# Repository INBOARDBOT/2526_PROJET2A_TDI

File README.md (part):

# 2526_PROJET2A_TDI
Total Drive Immersion - Motion System

The objective of this project is to create a 3 axis motion plateform for car racing simulations.
It consist of four linear actuators (with their respective [**drivers**](https://github.com/INBOARDBOT/2526_PROJET2A_TDI/tree/main/HARDWARE/PCB'S/FOC_CONTROLLER_V2)), a Nucleo Discovery which handle
the communication between the drivers and the computer as well as a touchscreen interface.
The data is sent from SimHub to the the Nucleo via UART. The position values are then distributed to each actuator via an [**RS485**](https://github.com/INBOARDBOT/2526_PROJET2A_TDI/tree/main/HARDWARE/PCB'S/COM_BOARD) bus.

# Achitecture logicielle

L'architecture logicielle est conçue de manière modulaire, segmentant les fonctionnalités du simulateur de conduite en plusieurs sous-systèmes spécialisés. Cette approche permet de séparer les responsabilités et de faciliter la maintenance du système. L'architecture s'articule autour de trois piliers principaux :

Couche Communication : Gère les protocoles d'échange de données entre l'unité centrale et les drivers de vérins (via le bus RS-485), garantissant l'intégrité et la rapidité des transmissions.

Module de Gestion des Actionneurs : Assure le traitement des commandes, le calcul des trajectoires des vérins et le monitoring de l'état des drivers.

Interface Graphique et IHM : Pilote le rendu visuel sur l'écran LCD-TFT et traite les interactions tactiles de l'utilisateur, tout en gérant les ressources stockées en mémoire Flash.

## Organistaion du projet
<br>
* `Application/` Contient la logique métier principale développée par l'utilisateur.
    * `gui/` et `generated/` Dédiés à l'interface graphique (typiquement pilotés par TouchGFX sur le F746G). Regroupe le backend (logique) et le frontend (assets et code généré).
    * `Core/` Noyau de l'application gérant la communication et la supervision de la centrale avec le reste du système de simulation.
* `Driver/` Regroupe les couches d'abstraction matérielle (BSP : gestion des composants externes). 
* `Debug/` Répertoire de sortie du compilateur.

## Présentation des Composants

### Unité Centrale
<br>
La centrale controle l'enssemble du systeme de simulation, elle doit etre reactive et embarquer une interface graphique servant d'IHM. Voici donc les principales fonctionnalites que la carte STM32F746G nous propose :
* Puissance de calcul : Architecture Arm Cortex STM32F746NGH6
* Interactions avec l'utilisateur (IHM) : Ecran tactile 4.3” RGB 480×272 color LCD-TFT
* Stockage des ressources graphiques lourdes commes les imges : 128-Mbit Quad-SPI Flash memory

Fonctionnalitees addiotionnelles petinentes :
* Gestion Audio intégrée : Audio line in and line out jack & Stereo speaker outputs

### Driver de vérin
<br>
Les drivers des verrins permettent de faire l'interface entre les ordres transmis par la centrale et l'action entrepris par les verrins. 
Les drivers des verrins permettent de communiquer via le bus RS485 afin de recevoir les données de position et de renvoyer des informations sur l'etat de l'actionneur.Il est compose des elements suivants :
* STSPIN32G4: Gère les calculs d'asservissemntet  le controle de l'etage de puissance grâce a son driver de mosfet intégré.
* STL130N8F7: L'etage de puissance est composé de trois demi pont avec des N-MOS pouvant supporter jusqu'a 80V et 100A 
* THVD1420: Tranciever RS485 

### Interface de Communication (Bus RS-485)
<br>
L'interface de communication est une carte électronique intermédiaire positionnée entre l'unité centrale et les différents actionneurs (vérins).

Pour surmonter la contrainte de la distance physique et garantir une transmission rapide et immunisée contre les parasites, la liaison s'appuie sur la norme RS-485. Ce standard utilise une signalisation différentielle particulièrement fiable en milieu industriel.

L'interface assure la conversion des signaux : elle transforme le protocole UART (TTL) de la centrale en signaux différentiels pour le bus, puis les drivers des vérins effectuent la conversion inverse pour traiter l'information. L'ensemble des drivers est raccordé en parallèle selon une topologie en bus, permettant une gestion simplifiée du câblage.

## Environnement de Développement
Le développement du projet repose sur une chaîne d'outils intégrée, permettant de gérer aussi bien la configuration matérielle que l'interface utilisateur et le versionnage du code.

`STM32CubeIDE` <br>
Il s'agit de l'environnement de développement (IDE) fourni par STMicroelectronics.

* Configuration : Intègre STM32CubeMX pour configurer graphiquement les périphériques (UART, RS-485, Horloges).

* Développement & Debug : Permet l'écriture du code en C/C++ et offre des outils de débogage avancés (lecture de registres en temps réel, analyseur de variables).

`TouchGFX Designer` <br>
Framework graphique avancé spécifiquement optimisé pour les microcontrôleurs STM32.

* Design UI : Permet de concevoir l'interface de manière visuelle pour ensuite developper en C++ dessus.

* CMSIS-RTOS : S'intègre avec FreeRTOS pour séparer le thread de rendu graphique des threads de communication et de calcul (Backend/Frontend).

* Generation du fichier du projet : Génére le code d'initialisation avec la configuration de l'interface graphique automatise (gros avantage de TouchGFX).

# Interface Graphique
<br>
L'interface graphique (IHM) permet de visualiser en temps réel l'état du système de simulation. Elle offre à l'utilisateur une plateforme interactive pour piloter le simulateur, lancer les procédures de calibration et ajuster les paramètres de conduite.

## TouchGFX Designer
TouchGFX Designer est l'outil utilisé pour concevoir l'environnement visuel. Il génère un code C++ optimisé qui tire parti des capacités d'accélération matérielle du STM32.

### Creation du projet
La première étape consiste à sélectionner le BSP (Board Support Package) correspondant à notre matériel : le `STM32F746G Discovery Kit`.<br>
<br>

[!IMPORTANT] Cette étape est cruciale car TouchGFX génère non seulement l'interface, mais aussi toute la structure du projet (fichiers de configuration, drivers d'écran, gestion de la mémoire) que nous importerons ensuite dans STM32CubeIDE.

### Architecture de l'interface
L'interface est découpée en plusieurs Écrans (Screens). Chaque écran possède son propre fichier de vue (View) et son présentateur (Presenter), permettant de séparer la logique graphique de la logique métier.

#### Ecran
Les vues du simulateur
Pour garantir une navigation fluide, nous avons segmenté l'IHM en quatre écrans principaux :

* SimHubScreen : Le tableau de bord principal. Il affiche les données télémétriques en temps réel, telles que l'extension des vérins et la consommation électrique des drivers.

* LoadingScreen : Une interface de transition utilisée lors des processus lourds, typiquement durant la phase de calibration automatique des vérins.

* MenuScreen : Le point d'entrée central permettant à l'utilisateur de naviguer entre les différentes sections.

* SettingScreen : Un espace dédié à la configuration logicielle et matérielle du système.

<br>

Avoir une multitude d'ecran permet de faciliter le developpement des differents UI. 

#### Composants et Outils
L'IDE propose deux types de blocs de construction pour concevoir les écrans :

1. Les Widgets : Ce sont les éléments de base (boutons, zones de texte, jauges, formes géométriques). Ils sont entièrement personnalisables pour correspondre à la charte graphique du simulateur.

2. Les Conteneurs (Containers) : Ils permettent de regrouper plusieurs widgets au sein d'une même entité. Cela facilite la création de fenêtres modales, de listes déroulantes ou de menus complexes.

Vous pouvez retrouver ci-dessous la documentation sur les outils et conteneurs pour en apprendre d'avantages [Contenuer/Outil](https://support.touchgfx.com/docs/development/ui-development/working-with-touchgfx/widgets-and-containers)

### Generer le projet
Une fois le design finalisé, l'outil génère le code source. Ce processus inclut :

* La conversion des images en tableaux de données stockés en Flash QSPI.

* L'implémentation de l'API graphique compatible avec FreeRTOS.

* La configuration des périphériques de la carte (écran, tactile, DMA2D).

[!NOTE] Bien que TouchGFX Designer soit puissant, il se limite à la couche visuelle. Les interactions complexes (ex: cliquer sur un bouton pour activer un vérin) nécessitent une implémentation manuelle dans le code C++ généré, via des fonctions de rappel (Callbacks).

## Backend and Frontend communication
Le défi majeur consiste à faire communiquer l'interface utilisateur avec le reste du système (capteurs, bus RS-485). TouchGFX utilise une architecture structurée pour séparer l'affichage de la logique métier.<br>

Définitions
* Le Frontend (La Vue) : Comprend les composants visibles à l'écran. Il est responsable de l'affichage des données et de la capture des interactions utilisateur.

* Le Backend (Le Système) : Représente tout ce qui se passe en dehors de l'interface (réception des données RS-485, calculs de trajectoires, mesures de courant).

L'Architecture MVP (Model-View-Presenter)<br>
<br>
Pour assurer une synchronisation fluide sans bloquer l'affichage, TouchGFX s'appuie sur trois couches :

1. Le Model : C'est le point d'entrée du Backend. Il reçoit les événements extérieurs (ex: nouvelle mesure de courant) et les stocke temporairement.

2. Le Presenter : Il agit comme un pont. Il surveille les changements dans le Model et ordonne à la View de se mettre à jour.

3. La View : Elle reçoit les ordres du Presenter et modifie visuellement les widgets (ex: mettre à jour la valeur d'une jauge).

vous pouvez visualiser cette video qui explique en detail comment afficher une valeur sur l'interface graphique [video](https://www.youtube.com/watch?v=Y7d6-59YQu8)

# Protocole de Communication
Comme expliqué précédemment, la liaison entre la centrale et les drivers repose sur une couche physique RS-485. Bien que les signaux en entrée et en sortie de l'interface soient au format UART, le support physique RS-485 permet de transporter ces données sur de longues distances tout en supportant une topologie réseau de type "Bus".

## Architecture Maître-Esclave
Pour organiser les échanges sur ce canal partagé, nous utilisons une architecture Maître-Esclave :

* Le Maître (Centrale) : Il est l'unique initiateur de la communication. Il interroge ou envoie des ordres aux drivers.

* Les Esclaves (Drivers) : Ils "écoutent" en permanence le bus et ne répondent ou n'agissent que lorsqu'ils sont explicitement sollicités par le maître.

## Principe du Bus de Communication 
Dans cette configuration, tous les esclaves sont branchés en parallèle sur la même ligne physique. Pour éviter que tous les vérins ne s'activent en même temps, nous utilisons un système d'adressage et de trames de données : <br>
<br>

1. L'Adressage : Chaque driver possède un identifiant unique (ID). Le message envoyé par la centrale commence par l'adresse de destination.

2. Le Filtrage : Tous les drivers reçoivent le signal, mais seul l'esclave dont l'adresse correspond à celle contenue dans le message traite l'information. Les autres ignorent la trame.

3. Les Données (Payload) : Une fois l'adresse validée, l'esclave décode les instructions (ex: consigne de position, vitesse, ou demande d'état).

## Gestion du flux (Half-Duplex)
<br>
Le bus RS-485 utilisé est généralement Half-Duplex : la centrale et les drivers partagent la même paire de fils pour émettre et recevoir.

Point d'attention : La centrale doit libérer le bus (repasser en mode réception) immédiatement après avoir envoyé une commande pour permettre à l'esclave de renvoyer son accusé de réception ou ses données de télémétrie.

## Structure de communication
<p align="justify">Afin d'optimiser les échanges de données avec les quatre esclaves du système, nous utilisons un protocole de cycle séquentiel. Le maître initie une transmission/réception itérative de l'esclave 0 à l'esclave 3. Au cours de chaque cycle, le maître récupère l'intégralité des données de l'esclave ciblé et les traite avant de passer au suivant. </p>

### Paquet de Données
<p align="justify">Le paquet de données est l'élément central de notre protocole. Il agit comme un conteneur standardisé permettant de transporter efficacement les commandes et les retours d'état.</p>

Voici la structure logicielle du paquet :

```
typedef struct __attribute__((packed))
{
    uint8_t startByte;   
    uint8_t address;     
    uint8_t cycleId;     
    
    uint8_t statusFlags; 
    uint8_t payloadCount; 

    union {
        struct {
            uint8_t type;    
            uint8_t code;    
        } fifoEntries[MAX_DATA / 2];

        uint16_t infoArray[MAX_DATA / 2]; 
        
        uint8_t rawBytes[MAX_DATA];
    } payload;

    uint8_t checksum;
    uint8_t stopByte;    
} MotionPacket_t;
```

Caractéristiques de Transmission
* <p align="justify">Standard UART : Le type uint8_t est utilisé comme unité de base, conformément au standard de communication série UART.</p>

* <p align="justify">Résolution des données : Les données système (telles que celles fournies par SimHub) sont quantifiées sur 16 bits. Par conséquent, chaque valeur dans infoArray occupe deux octets (uint8_t) lors de la transmission série.</p>

### Flag 
Les `Flags` ou `Drapeaux` en francais sont des informations actuelles sur le systeme d'une longueur d'un seul bit. Voici les differents que s'echangent le master et les slaves.

_Flag Master_
| Flag info     | Position bit  |
| ------------- |:-------------:|
| ACK_REQUEST   | 0             |
| CYCLE_ID_RST  | 1             |
| EMPTY_DATA    | 2             |
| TO_DEFINE     | 3             |
| TO_DEFINE     | 4             |
| TO_DEFINE     | 5             |
| TO_DEFINE     | 6             |
| TO_DEFINE     | 7             |

EMPTY_DATA   : Inform the slave it doesn't need to look for data in the packet <br>
CYCLE_ID_RST : Inform the slave the cycle id is reset (to 0) <br>
ACK_REQUEST  : Inform the slave to respond with flag ACK <br>

_Flag Slave_
| Flag info     | Position bit  |
| ------------- |:-------------:|
| ACK           | 0             |
| INIT_DONE     | 1             |
| MOTOR_EN      | 2             |
| MOTOR_MOVING  | 3             |
| BUSY          | 4             |
| EMPTY_DATA    | 5             |
| EMPTY_STATUS  | 6             |
| TO_DEFINE     | 7             |

ACK          : Inform the master that his message is acknowledged<br>
INIT_DONE    : Inform the master the initialisation is done (the system is calibrated)<br>
MOTOR_EN     : Inform the master that the motor are enabled to move<br>
MOTOR_MOVING : Inform the master the motor are moving<br>
BUSY         : Inform the master the slave can't take instruction at the moment<br>
EMPTY_DATA   : Inform the master to not look for data<br>
EMPTY_STATUS : Inform the master to not look for errors or events<br>

### Evenements
Les événements sont des alertes asynchrones envoyées par les esclaves pour informer d'un changement d'état opérationnel.<br>

Voici la liste evenements :
_Flag Slave_
| Evenement              | Code           |
| ---------------------- |:--------------:|
| EVT_NONE               | 0x00           |
| EVT_MOVEMENT_STARTED   | 0x01           |
| EVT_MOVEMENT_COMPLETED | 0x02           |
| EVT_TARGET_REACHED     | 0x03           |
| EVT_LIMIT_SWITCH_MIN   | 0x04           |
| EVT_LIMIT_SWITCH_MAX   | 0x05           |
| EVT_HOMING_STARTED     | 0x06           |
| EVT_HOMING_COMPLETED   | 0x07           |
| EVT_DRIVER_ONLINE      | 0x08           |
| EVT_DRIVER_OFFLINE     | 0x09           |
| EVT_PARAM_CHANGED      | 0x0A           |
| EVT_PLAYMODE_ON        | 0x0B           |
| EVT_PLAYMODE_OFF       | 0x0C           |
| EVT_INITMODE_ON        | 0x0D           |
| EVT_INITMODE_OFF       | 0x0E           |
| EVT_SLEEPMODE_ON       | 0x0F           |
| EVT_SLEEPMODE_OFF      | 0x10           |
| EVT_CALIB_STARTED      | 0x11           |
| EVT_CALIB_COMPLETED    | 0x12           |
| EVT_PARKED             | 0x13           |

EVT_NONE : No event <br>              
EVT_MOVEMENT_STARTED : The slave piston has started its movement <br>  
EVT_MOVEMENT_COMPLETED : The slave piston has completed its movement<br>
EVT_TARGET_REACHED : The slave piston is a the requested position<br>    
EVT_LIMIT_SWITCH_MIN : The slave piston is at the minimum position<br>  
EVT_LIMIT_SWITCH_MAX : The slave piston is at the maximum position<br>  
EVT_HOMING_STARTED : The slave piston is performing homing<br>    
EVT_HOMING_COMPLETED : The slave piston has completed its homing<br>  
EVT_DRIVER_ONLINE : The slave is now offline wait to be restarted<br>     
EVT_DRIVER_OFFLINE : The slave is now online and can perform operation <br>     
EVT_PARAM_CHANGED : The slave has succesfully changed its parameter <br>     
EVT_PLAYMODE_ON : The slave is ready for gaming <br>     
EVT_PLAYMODE_OFF : The slave is not ready for gaming <br>     

### Erreurs
Les erreurs sont des alertes asynchrones signalant un dysfonctionnement ou une anomalie sur un esclave.<br>

Voici la liste erreurs :
| Erreur                 | Code           |
| ---------------------- |:--------------:|
| ERR_NONE               | 0x00           |
| ERR_INVALID_COMMAND    | 0x01           |
| ERR_INVALID_PARAM      | 0x02           |
| ERR_TIMEOUT            | 0x03           |
| ERR_CHECKSUM_FAIL      | 0x04           |
| ERR_UNSUPPORTED        | 0x05           |
| ERR_STALL_DETECTED     | 0x06           |
| ERR_UNDERVOLTAGE       | 0x07           |
| ERR_UNDERVOLTAGEMCU    | 0x08           |
| ERR_FAILED_CALIB       | 0x09           |
| ERR_FAILED_SET_PIS_POS | 0x0A           |
| ERR_COMM_LOST          | 0x0B           |
| ERR_FRAME_INVALID      | 0x0C           |
| ERR_OVERHEATING        | 0x10           |
| ERR_OVERCURRENT        | 0x11           |
| ERR_OVERVOLTAGE        | 0x12           |
| ERR_OVERVOLTAGEMCU     | 0x13           |

Les erreurs critiques se différencient par le préfixe 0x1-. Elles entraînent généralement une mise en sécurité immédiate du matériel.<br>

ERR_NONE : No error <br>
ERR_INVALID_COMMAND : Command instruction not found <br>    
ERR_INVALID_PARAM : Packet parameter is invalid <br>      
ERR_TIMEOUT : Slave sends it when it takes too much time to do an operation<br>            
ERR_CHECKSUM_FAIL : Checksum of packet failed <br>              
ERR_STALL_DETECTED : Piston does not move even though it is instructed to (physical struggle) <br>    
ERR_UNDERVOLTAGE : Piston under voltage <br>      
ERR_UNDERVOLTAGEMCU : MCU is under voltage <br>   
ERR_FAILED_CALIB : Slave failed calibration <br>      
ERR_FAILED_SET_PIS_POS : Slave failed to set to the correct position <br>
ERR_COMM_LOST : Slave lost communication with master <br>         
ERR_FRAME_INVALID : Packet structure is giberish <br>     
ERR_OVERHEATING : Critic error piston is over heating <br>       
ERR_OVERCURRENT : Critic error piston is short circuiting <br>       
ERR_OVERVOLTAGE : Critic error piston is over voltage <br>       
ERR_OVERVOLTAGEMCU : Critic error MCU is over voltage <br>    

### Commandes

Les commandes sont les mots cles dans les paquets de transmission d'informations entre la centrale et les drivers.<br>

Voici la liste des differentes commandes :
| Commandes | Code | User |
| :--- | :---: | :--- |
| CMD_NOP | `0x00` | Master |
| CMD_PING | `0x01` | Master |
| CMD_GET_INFO | `0x02` | Master |
| CMD_RETURN_INFO | `0x03` | Slave |
| CMD_SET_STATE | `0x04` | Master |
| CMD_SET_MOTOR | `0x05` | Master |
| CMD_SET_PISTON | `0x06` | Master |

CMD_NOP : No cmd <br>
CMD_PING : Ping driver, waits for ping back to verify communication. Possibility to add a custom message to pinged device. data(64B, optional) : char* <br>
CMD_GET_INFO : Master request data from driver. data(1B) :  <br> 
| Instruction            | Position bit   |
| ---------------------- |:--------------:|
| POSITION               | 0              |
| SPEED                  | 1              |
| ACCELERATION           | 2              |
| TEMPERATURE            | 3              |
| MCU_VOLTAGE            | 4              |
| DRIVER_VOLTAGE         | 5              |
| DRIVER_STATE           | 6              |
| UNDEFINED              | 7              |
<br>

CMD_RETURN_INFO : Driver respond with requested data. data(14B) : <br>
| Instruction            | Position byte  |
| ---------------------- |:--------------:|
| POSITION               | 0-1            |
| SPEED                  | 2-3            |
| ACCELERATION           | 4-5            |
| TEMPERATURE            | 6-7            |
| MCU_VOLTAGE            | 8-9            |
| DRIVER_VOLTAGE         | 10-11          |
| DRIVER_STATE           | 12-13          |
| UNDEFINED              | ---            |
<br>
Pay attention that the response uses a `variable-length packed format`. But the requested values are appended sequentially without gaps. For example, requesting only POSITION and DRIVER_STATE will result in a 4-byte payload where the state immediately follows the position.

CMD_SET_STATE : Set the state of the driver. IN (1B) :  <br> 
| Instruction            | Position bit   |
| ---------------------- |:--------------:|
| SLEEP                  | 0              |
| INIT                   | 1              |
| PLAY                   | 2              |
| UNDEFINED              | 3              |
| UNDEFINED              | 4              |
| UNDEFINED              | 5              |
| UNDEFINED              | 6              |
| UNDEFINED              | 7              |
<br>

CMD_SET_MOTOR : Set the configuration of the motor. IN (1B) :  <br> 
| Instruction            | Position bit   |
| ---------------------- |:--------------:|
| MOTOR_ENABLE           | 0              |
| MOTOR_MOVEMENT         | 1              |
| UNDEFINED              | 2              |
| UNDEFINED              | 3              |
| UNDEFINED              | 4              |
| UNDEFINED              | 5              |
| UNDEFINED              | 6              |
| UNDEFINED              | 7              |
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
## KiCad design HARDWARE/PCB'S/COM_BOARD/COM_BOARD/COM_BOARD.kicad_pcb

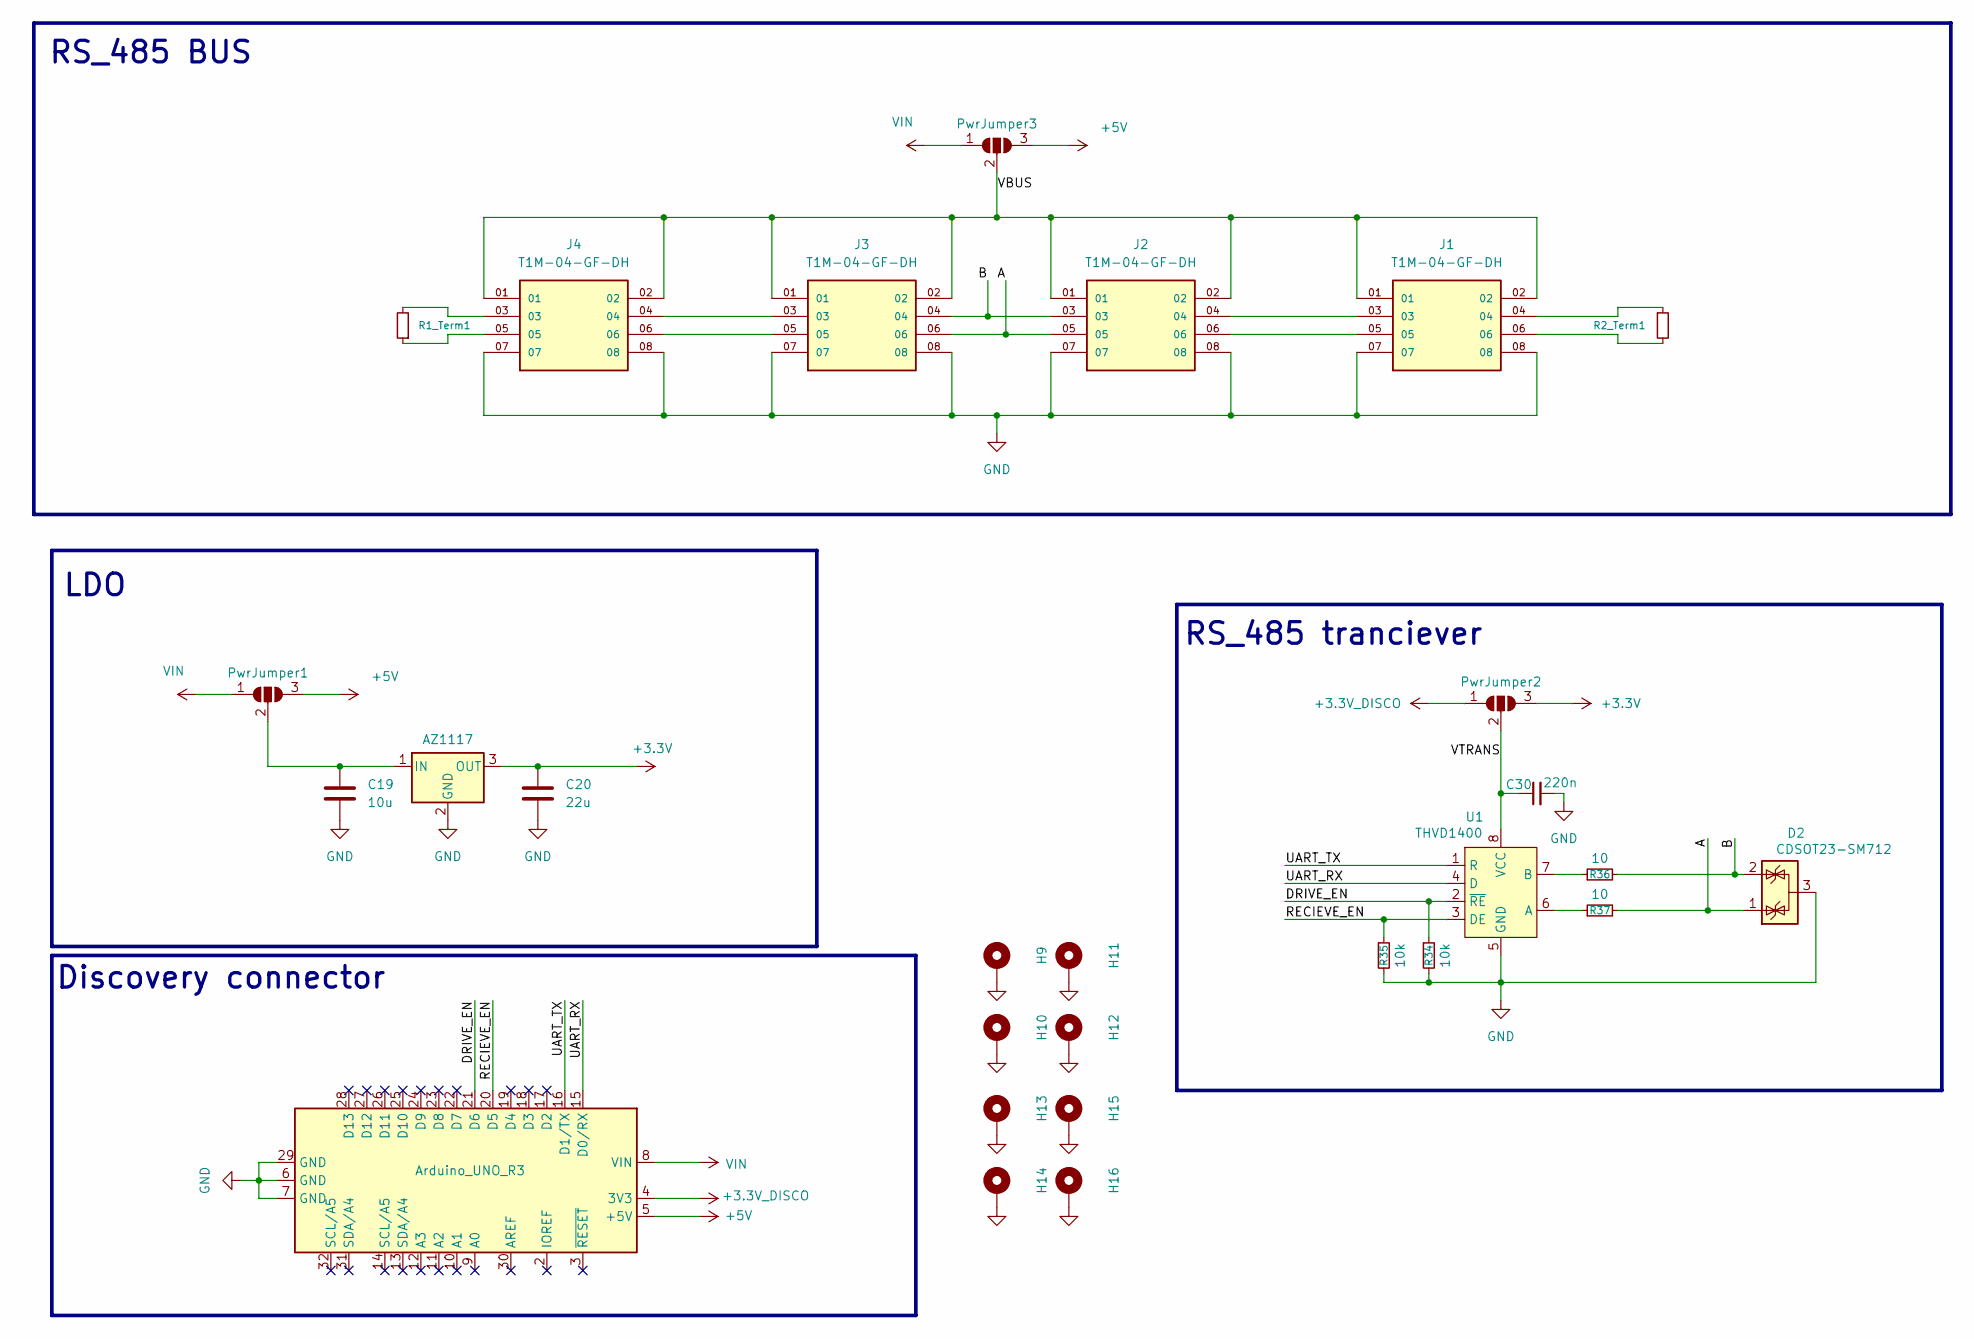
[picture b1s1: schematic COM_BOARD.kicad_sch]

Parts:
A1: Arduino_UNO_R3
C19: 10u; C_0805_2012Metric_Pad1.18x1.45mm_HandSolder
C20: 22u; C_0805_2012Metric_Pad1.18x1.45mm_HandSolder
C30: 220n; C_0603_1608Metric; MPN 885012207051
D2: CDSOT23-SM712; SOT-23
H9, H10, H11, H12, H13, H14, H15, H16: MountingHole_Pad; MountingHole_3.2mm_M3_Pad_Via
J1, J2, J3, J4: T1M-04-GF-DH; SAMTEC_T1M-04-GF-DH
J10: AZ1117; SOT-223
PwrJumper1, PwrJumper2, PwrJumper3: SolderJumper_3_Open; SolderJumper-3_P1.3mm_Open_RoundedPad1.0x1.5mm_NumberLabels
R1_Term1, R2_Term1: R_Small; R_0603_1608Metric
R34, R35: 10k; R_0603_1608Metric
R36, R37: 10; R_0603_1608Metric
U1: THVD1400; SOIC-8_3.9x4.9mm_P1.27mm

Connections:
+3.3V: C20.1, J10.3 (OUT), PwrJumper2.3 (B)
+3.3V_DISCO: A1.4 (3V3), PwrJumper2.1 (A)
+5V: A1.5 (+5V), PwrJumper1.3 (B), PwrJumper3.3 (B)
/A: D2.1 (K), J2.05, J3.06, R37.2
/B: D2.2 (K), J2.03, J3.04, R36.2
/DRIVE_EN: A1.21 (D6), R34.1, U1.2 (~RE)
/RECIEVE_EN: A1.20 (D5), R35.1, U1.3 (DE)
/UART_RX: A1.15 (D0/RX), U1.4 (D)
/UART_TX: A1.16 (D1/TX), U1.1 (R)
/VBUS: J1.01, J1.02, J2.01, J2.02, J3.01, J3.02, J4.01, J4.02, PwrJumper3.2 (C)
/VTRANS: C30.1, PwrJumper2.2 (C), U1.8 (VCC)
GND: A1.6 (GND), A1.7 (GND), A1.29 (GND), C19.2, C20.2, C30.2, D2.3 (A), H9.1, H10.1, H11.1, H12.1, H13.1, H14.1, H15.1, H16.1, J1.07, J1.08, J2.07, J2.08, J3.07, J3.08, J4.07, J4.08, J10.2 (GND), R34.2, R35.2, U1.5 (GND)
unnamed: J1.03, J2.04
unnamed: J1.04, R2_Term1.1
unnamed: J1.05, J2.06
unnamed: J1.06, R2_Term1.2
unnamed: J3.03, J4.04
unnamed: J3.05, J4.06
unnamed: J4.03, R1_Term1.2
unnamed: J4.05, R1_Term1.1
unnamed: C19.1, J10.1 (IN), PwrJumper1.2 (C)
unnamed: R37.1, U1.6 (A)
unnamed: R36.1, U1.7 (B)
VIN: A1.8 (VIN), PwrJumper1.1 (A), PwrJumper3.1 (A)

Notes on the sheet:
RS_485 tranciever
LDO
Discovery connector
RS_485 BUS

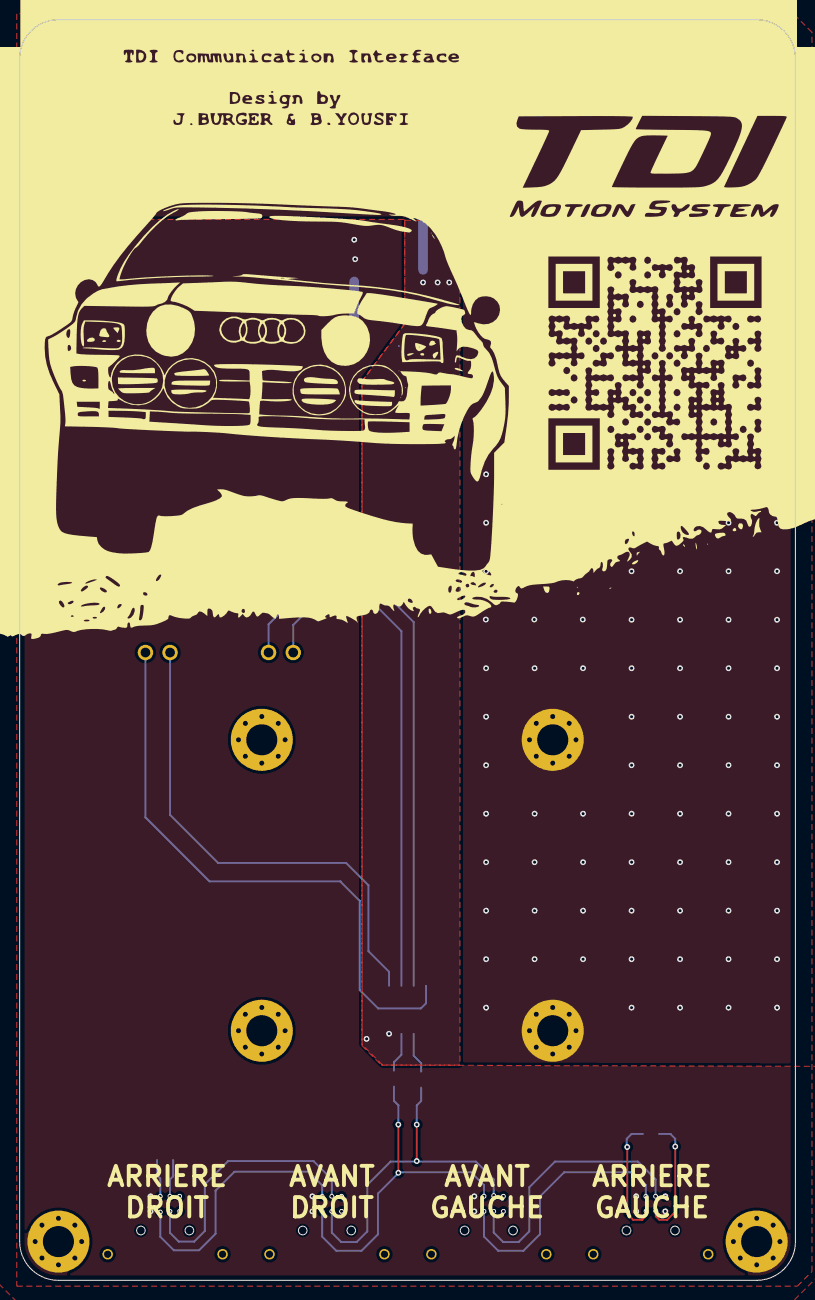
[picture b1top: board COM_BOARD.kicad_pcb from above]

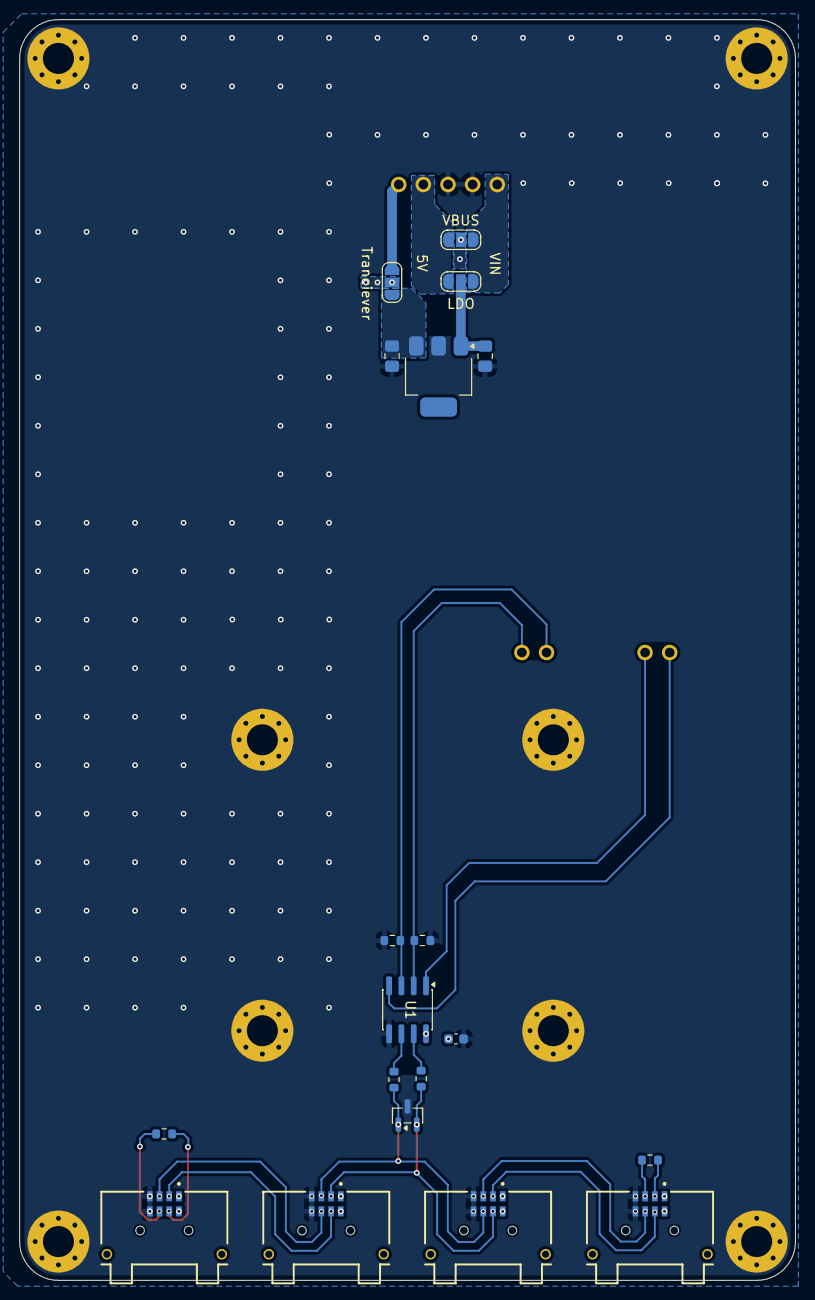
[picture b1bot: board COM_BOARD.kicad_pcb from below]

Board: 2 copper layers, 80.0 x 130.0 mm, 28 parts (20 on the bottom side), 24 nets.

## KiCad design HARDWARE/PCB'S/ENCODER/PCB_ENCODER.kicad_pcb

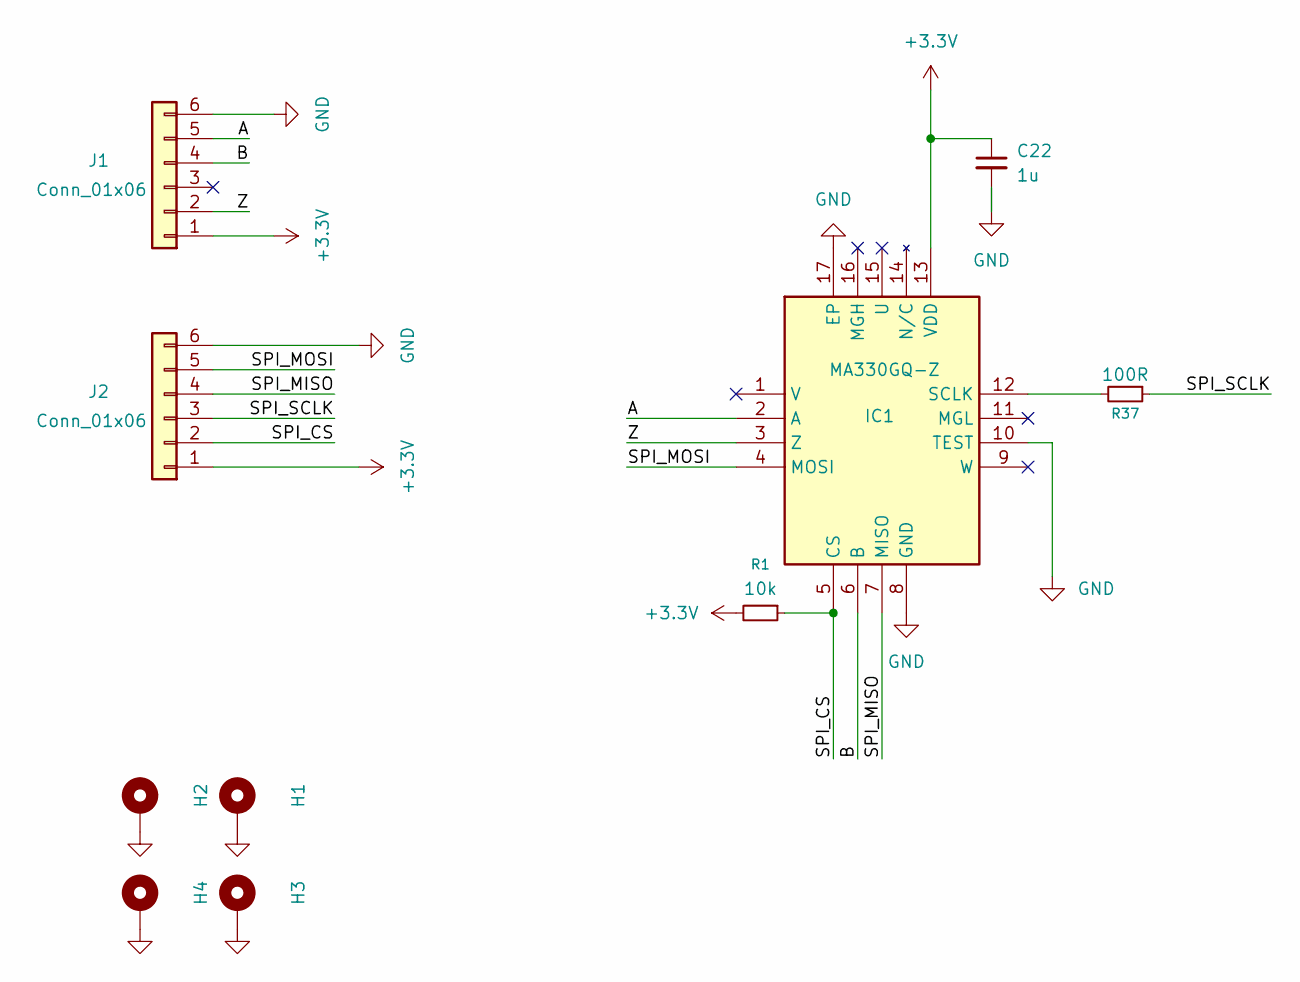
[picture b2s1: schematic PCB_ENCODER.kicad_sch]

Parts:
C22: 1u; C_0603_1608Metric
H1, H2, H3, H4: MountingHole_Pad; MountingHole_3.2mm_M3_Pad_Via
IC1: MA330GQ-Z; QFN-16-1EP_3x3mm_P0.5mm_EP1.7x1.7mm; Manufacturer_Part_Number MA330GQ-Z; Mouser Part Number 946-MA330GQ-Z
J1, J2: Conn_01x06; JST_GH_SM06B-GHS-TB_1x06-1MP_P1.25mm_Horizontal
R1: 10k; R_0603_1608Metric
R37: 100R; R_0603_1608Metric

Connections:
+3.3V: C22.1, IC1.13 (VDD), J1.1, J2.1, R1.2
/A: IC1.2 (A), J1.5
/B: IC1.6 (B), J1.4
/SPI_CS: IC1.5 (CS), J2.2, R1.1
/SPI_MISO: IC1.7 (MISO), J2.4
/SPI_MOSI: IC1.4 (MOSI), J2.5
/SPI_SCLK: J2.3, R37.1
/Z: IC1.3 (Z), J1.2
GND: C22.2, H1.1, H2.1, H3.1, H4.1, IC1.8 (GND), IC1.10 (TEST), IC1.17 (EP), J1.6, J2.6
unnamed: IC1.12 (SCLK), R37.2

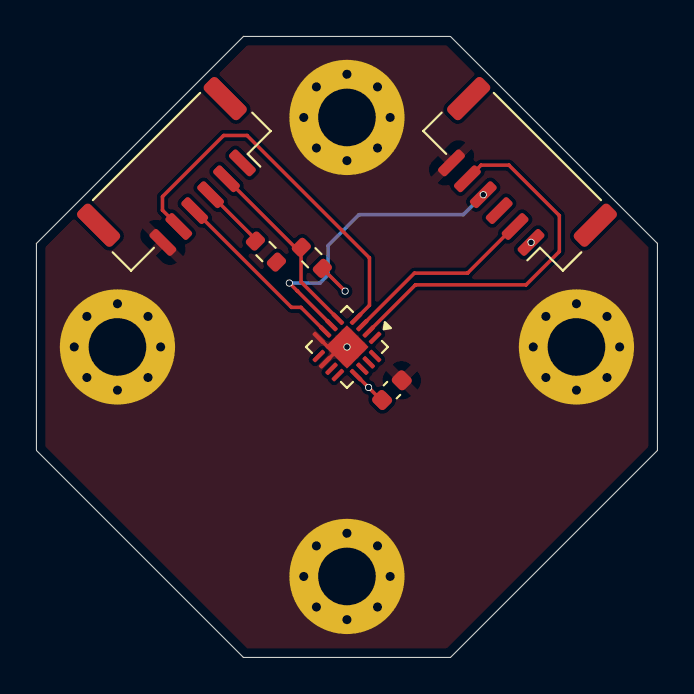
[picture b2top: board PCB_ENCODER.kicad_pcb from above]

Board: 2 copper layers, 34.5 x 34.5 mm, 10 parts (0 on the bottom side), 10 nets.

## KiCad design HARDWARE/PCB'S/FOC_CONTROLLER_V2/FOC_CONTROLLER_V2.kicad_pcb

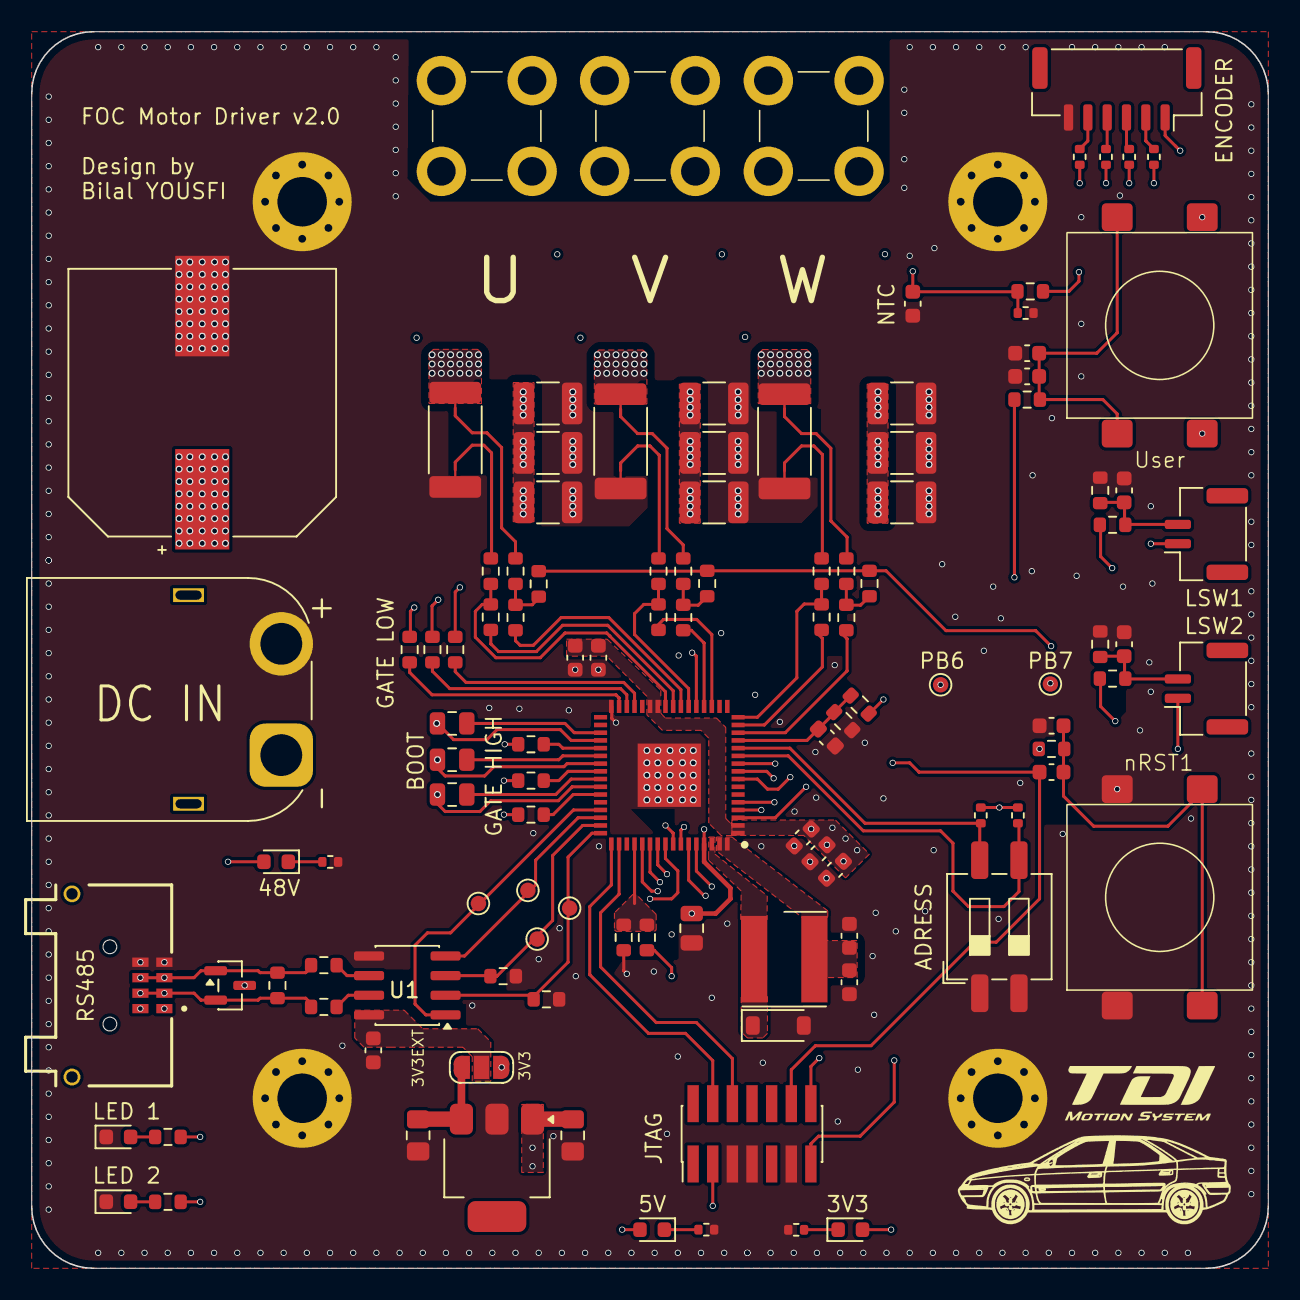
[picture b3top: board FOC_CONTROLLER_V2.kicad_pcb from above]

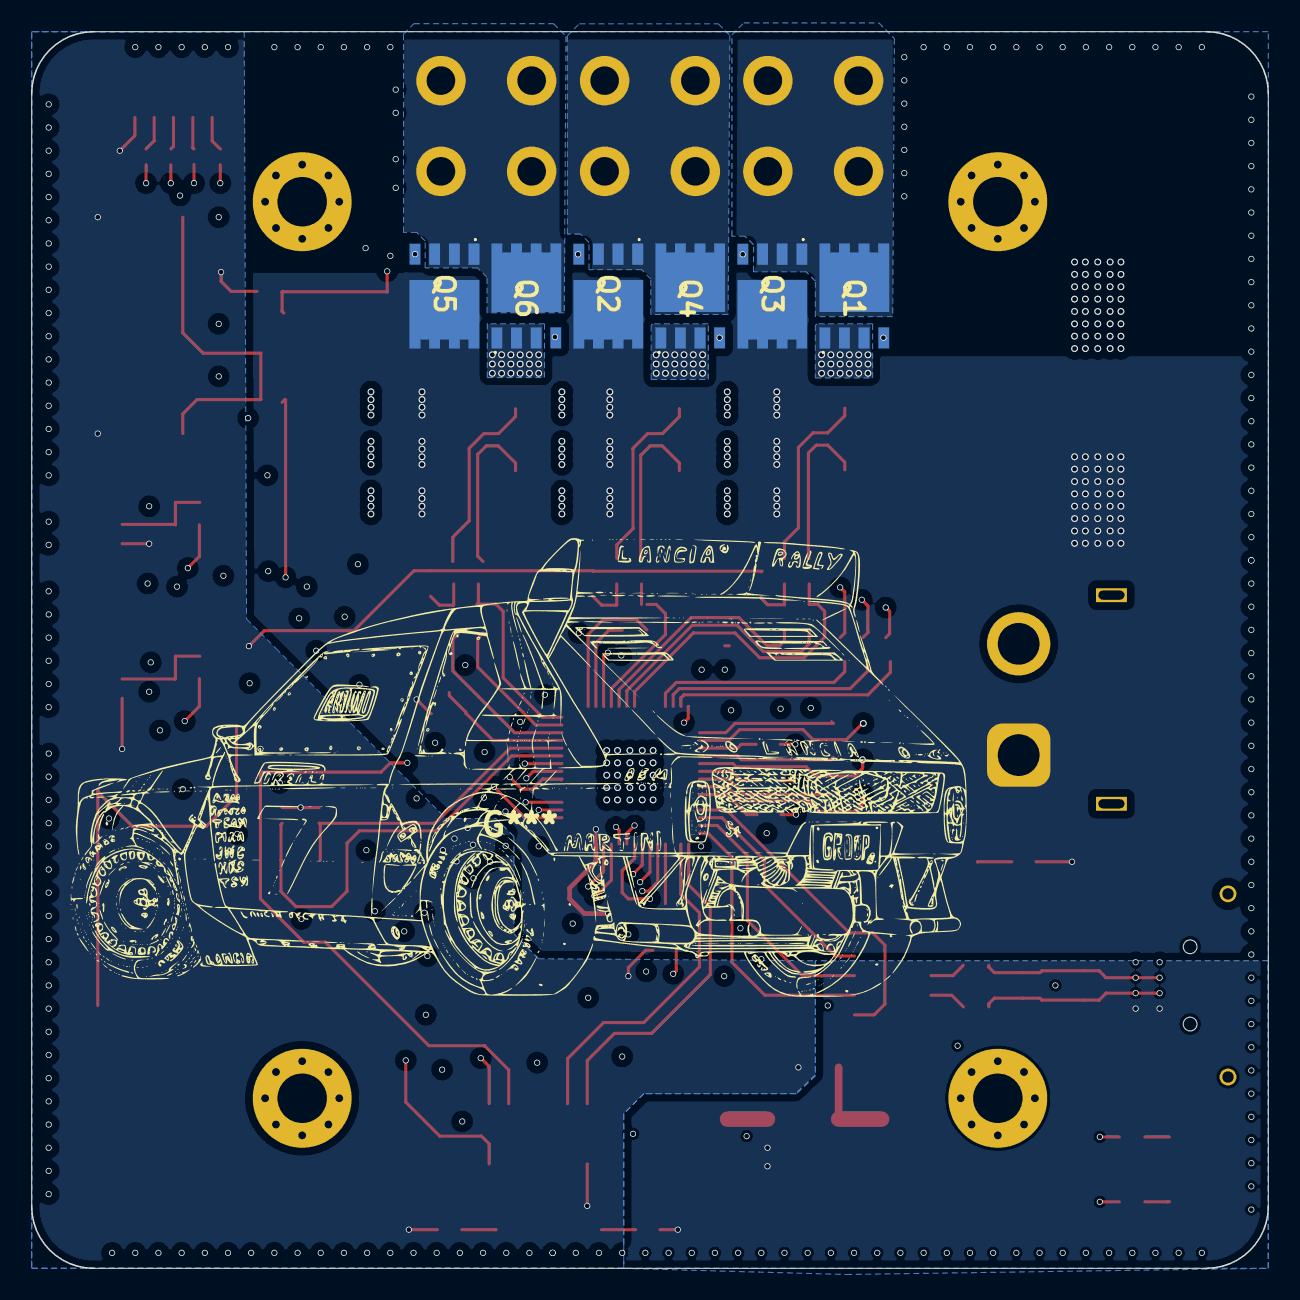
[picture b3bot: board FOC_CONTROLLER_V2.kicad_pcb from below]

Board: 4 copper layers, 80.0 x 80.0 mm, 124 parts (6 on the bottom side), 89 nets.

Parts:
C1, C3, C5: 1u; C_0805_2012Metric
C2: 220u; CP_Wurth_WCAP-ASLL-D16L17
C4, C6: 220n; C_1210_3225Metric_Pad1.33x2.70mm_HandSolder
C8: 220n; C_0805_2012Metric
C9, C11, C12, C15, C18, C28, C29: 100n; C_0603_1608Metric
C10: 2.2u; C_0603_1608Metric
C13: 10u; C_0603_1608Metric
C14: 1u; C_0603_1608Metric
C16: N.M.; C_0603_1608Metric
C17, C24: 33n; C_0603_1608Metric
C19: 10u; C_0805_2012Metric_Pad1.18x1.45mm_HandSolder
C20: 22u; C_0805_2012Metric_Pad1.18x1.45mm_HandSolder
C21, C22, C26, C27, C31, C32, C33: N.M.; C_1210_3225Metric_Pad1.33x2.70mm_HandSolder
C30: 220n; C_0603_1608Metric
D1, D3, D5, D8, D9: LED; LED_0603_1608Metric
D2: CDSOT23-SM712; SOT-23
D4: STPS0560Z; D_SOD-123
H1, H2, H3, H4: MountingHole_Pad; MountingHole_3.2mm_M3_Pad_Via
IC1: STSPIN32G4; QFN50P900X900X100-65N-D
J1: DC IN; AMASS_XT60PW-M_1x02_P7.20mm_Horizontal
J2, J3, J4: Conn_01x01; REDCUBETHT_74651173R
J6: JTAG; PinHeader_2x07_P1.27mm_Vertical_SMD
J10: AZ1117; SOT-223
J11: T1M-04-GF-DH; SAMTEC_T1M-04-GF-DH
J12: Conn_01x06; JST_GH_SM06B-GHS-TB_1x06-1MP_P1.25mm_Horizontal
L1: 15u; L_Wurth_WE-MXGI-5030
LSW1, LSW2: Conn_SW_2; JST_GH_SM02B-GHS-TB_1x02-1MP_P1.25mm_Horizontal
NTC1: 10K; R_0603_1608Metric
PwrJumper1: SolderJumper_3_Open; SolderJumper-3_P1.3mm_Open_RoundedPad1.0x1.5mm_NumberLabels
Q1, Q4, Q6: CSD18543Q3A; CSD18540Q5BT
Q2, Q3, Q5: CSD19534Q5A; CSD18540Q5BT
R1, R3, R4, R5, R6, R7: 100; R_0603_1608Metric
R2: 22k; R_0603_1608Metric
R8, R49, R51: 100k; R_0603_1608Metric
R9: 200; C_0603_1608Metric
R10, R34, R35: 10k; R_0603_1608Metric
R11, R48: 330; R_0603_1608Metric
R12: 100k; C_0603_1608Metric
R13, R16, R18, R19, R23, R24: 1.5k; R_0603_1608Metric
R14, R15, R20, R21, R25, R26: 30K; R_0603_1608Metric
R17, R22, R27: 15k; R_0603_1608Metric
R28: 72.3k; R_0603_1608Metric
R29: 3.01k; R_0603_1608Metric
R30, R50, R52: 200; R_0603_1608Metric
R31, R32, R33: R_Shunt; R_2512_6332Metric_Pad1.40x3.35mm_HandSolder
R36, R37, R53: 10; R_0603_1608Metric
R38: 2k5; R_0402_1005Metric
R39: 1k5; R_0402_1005Metric
R40: 12k; R_0402_1005Metric
R41, R42, R43, R44: 200; R_0402_1005Metric
R45: 4.7k; R_0402_1005Metric
R46, R47: 10k; R_0402_1005Metric
SW3: SW_DIP_x02; SW_DIP_SPSTx02_Slide_6.7x6.64mm_W8.61mm_P2.54mm_LowProfile
TP1, TP2, TP3, TP4: 3V3; TestPoint_Pad_D1.0mm
TP14, TP15: 5V; TestPoint_Pad_D1.0mm
U1: THVD1400; SOIC-8_3.9x4.9mm_P1.27mm
User: SW_MEC_5G; DeBouton
nRST1: SW_MEC_5G; DeBouton

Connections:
+3,3V_EXT: C20.1, J10.3 (OUT), PwrJumper1.3 (B)
+3.3V: C10.1, C11.1, C12.1, C14.1, C15.1, D9.2 (A), IC1.1 (REG3V3/VDD), IC1.2 (VBAT), IC1.26 (VREF+), IC1.27 (VDDA), J6.3 (VCC), J12.1, LSW1.1, LSW2.1, NTC1.1, PwrJumper1.1 (A), R2.2, R8.1, R14.2, R20.2, R25.2, R46.2, R47.2, User.3 (B), User.4 (B)
+5V: C19.1, D8.2 (A), J10.1 (IN), J11.01, J11.02
+48V: C2.1, C4.2, C6.2, C8.1, C21.2, C22.2, C26.2, C27.2, C31.2, C32.2, C33.2, D5.2 (A), IC1.61 (VM), J1.1, Q2.5 (D), Q3.5 (D), Q5.5 (D), R28.1
/A: D2.1 (K), J11.05, J11.06, R37.2, R53.1
/ADD_SEL_0: IC1.12 (PC3), R47.1, SW3.4
/ADD_SEL_1: IC1.11 (PC2), R46.1, SW3.3
/Ampli_1/VSHUNTXN: R16.1, R31.2
/Ampli_1/VSHUNTXP: R18.1, R31.3
/Ampli_2/VSHUNTXN: R13.1, R32.2
/Ampli_2/VSHUNTXP: R19.1, R32.3
/Ampli_3/VSHUNTXN: R23.1, R33.2
/Ampli_3/VSHUNTXP: R24.1, R33.3
/B: D2.2 (K), J11.03, J11.04, R36.2, R53.2
/BOOT1: C1.1, IC1.41 (BOOT1)
/BOOT2: C3.1, IC1.38 (BOOT2)
/BOOT3: C5.1, IC1.35 (BOOT3)
/Conn_SW_1: C28.2, LSW1.2, R49.1, R50.1
/Conn_SW_2: C29.2, LSW2.2, R51.1, R52.1
/DRIVE_EN: IC1.48 (PA12), R34.1, TP2.1, U1.2 (~RE)
/GHS1: IC1.43 (GHS1), R4.1
/GHS2: IC1.40 (GHS2), R1.1
/GHS3: IC1.37 (GHS3), R6.1
/GLS1: IC1.29 (GLS1), R3.1
/GLS2: IC1.30 (GLS2), R5.1
/GLS3: IC1.31 (GLS3), R7.1
/L_SW_1: IC1.60 (PB9), R50.2
/L_SW_2: IC1.59 (PB8), R52.2
/NRST: IC1.8 (PG10), J6.12 (~RST), R9.2
/NTC: C24.2, IC1.21 (PC4), NTC1.2, R45.1
/OPN1: IC1.25 (PB2), R16.2, R17.1
/OPN2: IC1.22 (PC5), R13.2, R22.1
/OPN3: IC1.16 (PA3), R23.2, R27.1
/OPO1: IC1.24 (PB1), R17.2
/OPO2: IC1.19 (PA6), R22.2
/OPO3: IC1.15 (PA2), R27.2
/OPP1: IC1.23 (PB0), R15.1
/OPP2: IC1.20 (PA7), R21.1
/OPP3: IC1.14 (PA1), R26.1
/OUT1: C1.2, IC1.42 (OUT1), J2.1, Q1.5 (D), Q3.1 (S), Q3.2 (S), Q3.3 (S)
/OUT2: C3.2, IC1.39 (OUT2), J3.1, Q2.1 (S), Q2.2 (S), Q2.3 (S), Q4.5 (D)
/OUT3: C5.2, IC1.36 (OUT3), J4.1, Q5.1 (S), Q5.2 (S), Q5.3 (S), Q6.5 (D)
/PB6: IC1.57 (PB6), TP15.1
/PB7: IC1.58 (PB7), TP14.1
/RECIEVE_EN: IC1.47 (PA11), R35.1, TP1.1, U1.3 (DE)
/SPI_CS: J12.2, R44.2
/SPI_MISO: J12.4, R42.2
/SPI_MOSI: J12.5, R41.2
/SPI_SCLK: J12.3, R43.2
/SW: D4.1 (K), IC1.62 (SW), L1.1
/SWCLK: IC1.50 (PA14), J6.6 (JCLK/SWCLK)
/SWDIO: IC1.49 (PA13), J6.4 (JTMS/SWDIO)
/UART_RX: IC1.46 (PA10), TP3.1, U1.4 (D)
/UART_TX: IC1.45 (PA9), TP4.1, U1.1 (R)
/User: IC1.3 (PC13), R30.2
/VCP_RX: IC1.10 (PC1), J6.13 (VCP_RX)
/VCP_TX: IC1.9 (PC0), J6.14 (VCP_TX)
GND: C2.2, C4.1, C6.1, C8.2, C9.2, C10.2, C11.2, C12.2, C13.2, C14.2, C15.2, C16.2, C17.2, C18.1, C19.2, C20.2, C21.1, C22.1, C24.1, C26.1, C27.1, C28.1, C29.1, C30.2, C31.1, C32.1, C33.1, D1.1 (K), D2.3 (A), D3.1 (K), D4.2 (A), H1.1, H2.1, H3.1, H4.1, IC1.32 (PGND), IC1.65 (VSS), J1.2, J6.5 (GND), J6.7 (GND), J6.11 (GNDDetect), J10.2 (GND), J11.07, J11.08, J12.6, R10.1, R12.2, R29.2, R31.1, R32.1, R33.1, R34.2, R35.2, R38.2, R39.2, R40.2, R45.2, R49.2, R51.2, SW3.1, SW3.2, U1.5 (GND), nRST1.1 (A), nRST1.2 (A)
unnamed: C9.1, R8.2, R9.1, nRST1.3 (B), nRST1.4 (B)
unnamed: C18.2, R12.1, R30.1, User.1 (A), User.2 (A)
unnamed: D1.2 (A), R11.2
unnamed: D3.2 (A), R48.2
unnamed: D5.1 (K), R40.1
unnamed: D8.1 (K), R38.1
unnamed: D9.1 (K), R39.1
unnamed: C17.1, IC1.13 (PA0), R28.2, R29.1
unnamed: IC1.54 (PB3), R43.1
unnamed: IC1.55 (PB4), R42.1
unnamed: IC1.56 (PB5), R41.1
unnamed: IC1.4 (PC14), R11.1
unnamed: IC1.5 (PC15), R48.1
unnamed: IC1.53 (PD2), R44.1
unnamed: C13.1, C16.1, IC1.63 (VCC), IC1.64 (REGIN), L1.2
unnamed: IC1.52 (SCREF), R2.1, R10.2
unnamed: C30.1, PwrJumper1.2 (C), U1.8 (VCC)
unnamed: Q1.4 (G), R3.2
unnamed: Q1.1 (S), Q1.2 (S), Q1.3 (S), R31.4
unnamed: Q2.4 (G), R1.2
unnamed: Q3.4 (G), R4.2
unnamed: Q4.4 (G), R5.2
unnamed: Q4.1 (S), Q4.2 (S), Q4.3 (S), R32.4
unnamed: Q5.4 (G), R6.2
unnamed: Q6.4 (G), R7.2
unnamed: Q6.1 (S), Q6.2 (S), Q6.3 (S), R33.4
unnamed: R14.1, R15.2, R18.2
unnamed: R19.2, R20.1, R21.2
unnamed: R24.2, R25.1, R26.2
unnamed: R37.1, U1.6 (A)
unnamed: R36.1, U1.7 (B)

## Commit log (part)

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2025-09-16 aucun rapport avec le projet
2025-11-05 Upload core code
2025-11-05 Driver code for graphic and volatile memory
2025-11-05 Create driver repo
2025-11-05 addition of STM32 IDE configuration of the prject
2025-11-09 PCB v2
    Schematic
2025-11-17 Routage Phases PCB
2025-11-18 Routage PCB 99%
2025-11-19 PCB driver
    Routage terminé
    Verifier si l'USB C permet d'avoir un bus et non pas une topologie en étoile
2025-11-20 PCB driver : DONE
2025-11-20 PCB driver : Fabrication files
2025-11-20 Revert "PCB driver : Fabrication files"
    This reverts commit 97e42d653fb7943bf99489ddc4c3818d19a40daa.
2025-11-20 Fabrication files
2025-11-20 PCB driver : Graphics
2025-11-23 Communication board : done
2025-11-24 COM PCB : Tweaks
2025-11-24 PCB BOM : Fabrication files update
2025-11-25 no more FOC_CONTROLLER_V2 directory
    Plus de hardware dans le software
2025-12-11 Master-Slave sequence diagram
    Addition of Master-Slave Synchronization cycle sequence diagram
2025-12-11 Add master-slave synchronization cycle section
2025-12-11 Replace link with image for synchronization diagram
    Updated the README to display the synchronization diagram as an image.
2025-12-11 add masterslaveSync svg
2025-12-11 Update diagram link in README
2025-12-11 Update diagram file reference in README
2025-12-11 Fix image filename case in README.md
2025-12-11 Backend - Frontend Synchronization
2025-12-11 Add synchronization cycle diagrams to README
    Added synchronization cycle diagrams for Master-Slave and Backend-Frontend.
2026-01-12 Create Application
    Refresh project code software
2026-01-12 Create test
2026-01-12 refresh project
2026-01-13 Repo hardware rework
2026-01-13 Enhance README with project details and architecture
    Added detailed project architecture, components, and development environment sections to README.
2026-01-13 Refactor README structure and remove duplicates
    Removed redundant sections and reorganized content in the README.
2026-01-13 Enhance README with synchronization and communication details
    Added sections on synchronization cycles, communication protocols, and task management for the motion system.
2026-01-13 Revise README for clarity and update content
    Removed sections on project title and synchronization diagrams. Added details on events and errors for slave communication.
2026-01-13 add seq diag master slave cycle
2026-01-13 Replace synchronization diagrams in README
    Updated synchronization cycle diagrams in README.
2026-01-13 Adjust image sizes in README.md
    Updated image sizes in the README for better presentation.
2026-01-14 Readme update
2026-01-16 Update README with image for finite state machine
2026-01-16 Enlever le texte fais par gemini (IA) dans le readme
    Je me demande si les profs vont regarder tous les commit. j'espere pas.
2026-01-16 Update RTOS integration description in README
2026-01-16 Revise events, errors, and add command documentation
    Updated event and error lists, added command section with descriptions.
2026-01-16 Revise command and event tables in README
    Updated command table and added new event types.
2026-01-19 Revise README with synchronization and FSM details
    Updated section titles and added new content related to system synchronization and FSM.
2026-01-19 Add FSM communication image to README
2026-04-09 Bouger des fichiers
2026-04-09 Bouger des fichiers2
2026-04-10 Driver readme 1
2026-04-10 Driver readme 2
2026-04-10 Driver readme 3
2026-04-10 Driver readme 4
2026-04-10 Driver readme 5
2026-04-10 Driver readme 6
2026-04-28 Corrector_speed
